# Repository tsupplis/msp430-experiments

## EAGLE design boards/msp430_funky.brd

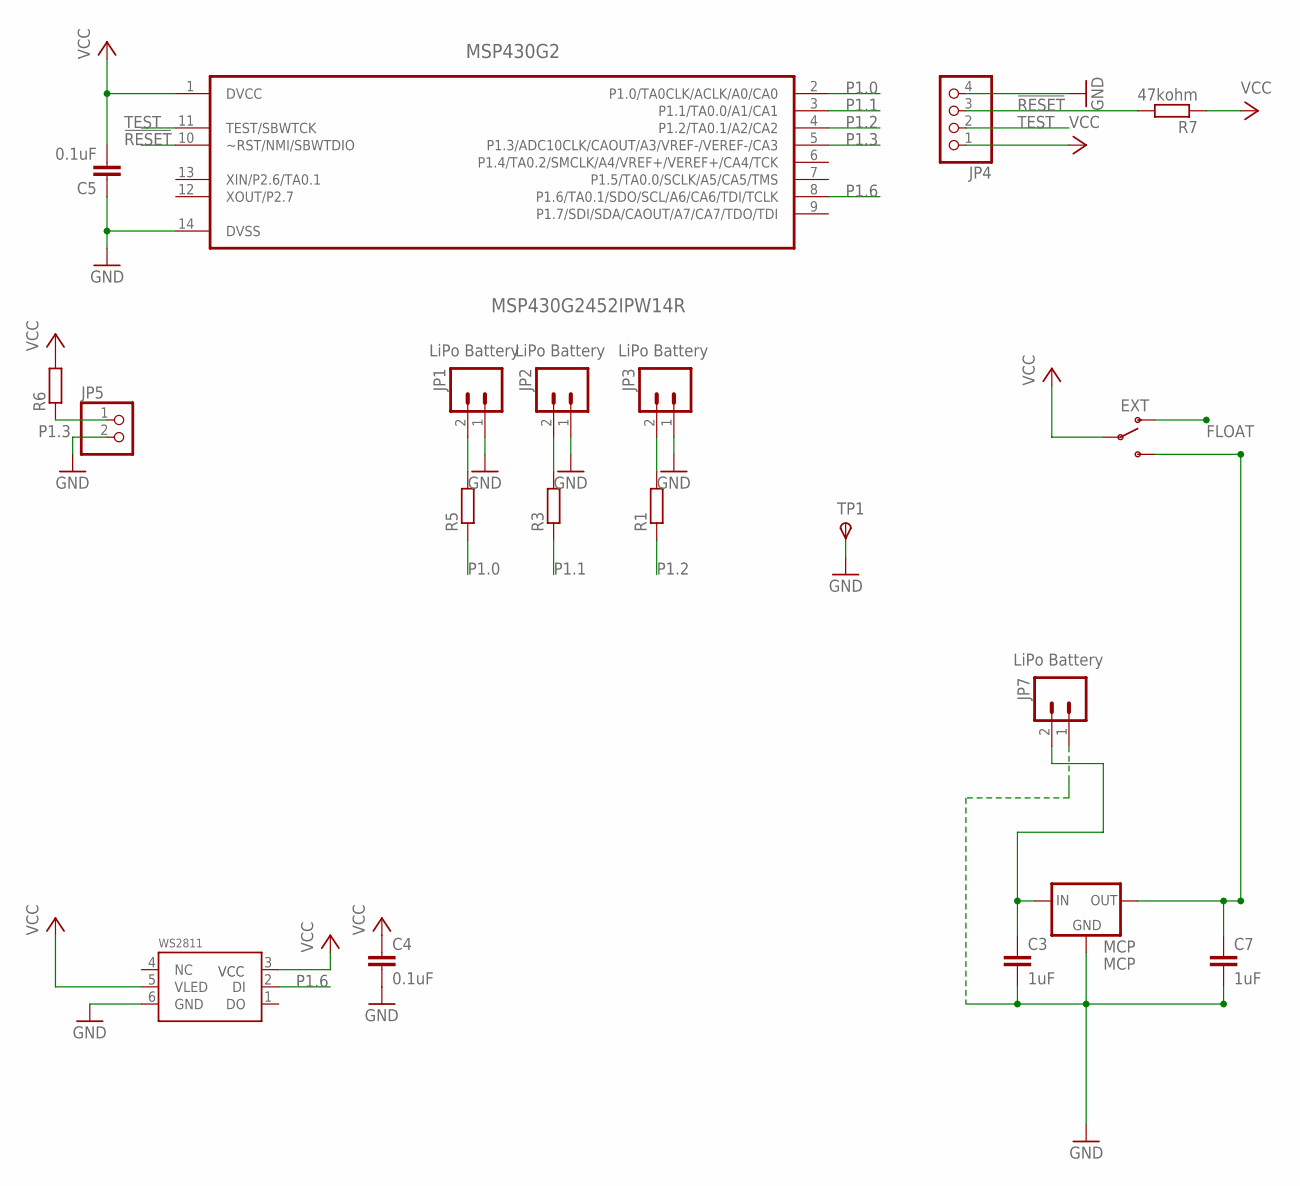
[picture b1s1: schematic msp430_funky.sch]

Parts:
C3, C7: 1uF; C0805
C4, C5: 0.1uF; C0805
JP1, JP2, JP3, JP7: LiPo Battery; JST-2-PTH
JP4: PINHD-1X4; 1X04
JP5: PINHD-1X2; 1X02
MCP: MCP; SOT-23
MSP430G2: MSP430G2452IPW14R; SOP65P640X120-14N
ON: EXT; SWITCH-SPDT
R1, R3, R5, R6: R-EU_R0805; R0805
R7: 47kohm; R0805
TP1: TPSTP20R; TP20R
WS2811: 5050WS2811W; RGBLED5050W

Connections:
!RESET: JP4.3, MSP430G2.10 (~RST/NMI/SBWTDIO), R7.2
FLOAT: ON.1 (O)
GND: C3.2, C4.2, C5.1, C7.2, JP1.1, JP2.1, JP3.1, JP4.4, JP5.2, JP7.1, MCP.1 (GND), MSP430G2.14 (DVSS), TP1.TP, WS2811.6 (GND)
unnamed: JP1.2, R5.2
unnamed: JP2.2, R3.2
unnamed: JP3.2, R1.2
P1.0: MSP430G2.2 (P1.0/TA0CLK/ACLK/A0/CA0), R5.1
P1.1: MSP430G2.3 (P1.1/TA0.0/A1/CA1), R3.1
P1.2: MSP430G2.4 (P1.2/TA0.1/A2/CA2), R1.1
P1.3: JP5.1, MSP430G2.5 (P1.3/ADC10CLK/CAOUT/A3/VREF-/VEREF-/CA3), R6.1
P1.6: MSP430G2.8 (P1.6/TA0.1/SDO/SCL/A6/CA6/TDI/TCLK), WS2811.2 (DI)
TEST: JP4.2, MSP430G2.11 (TEST/SBWTCK)
VCC: C4.1, C5.2, JP4.1, MSP430G2.1 (DVCC), ON.2, R6.2, R7.1, WS2811.3 (VCC), WS2811.5 (VLED)
VCCEXT: C3.1, JP7.2, MCP.3 (IN)
VCCREG: C7.1, MCP.2 (OUT), ON.3 (S)

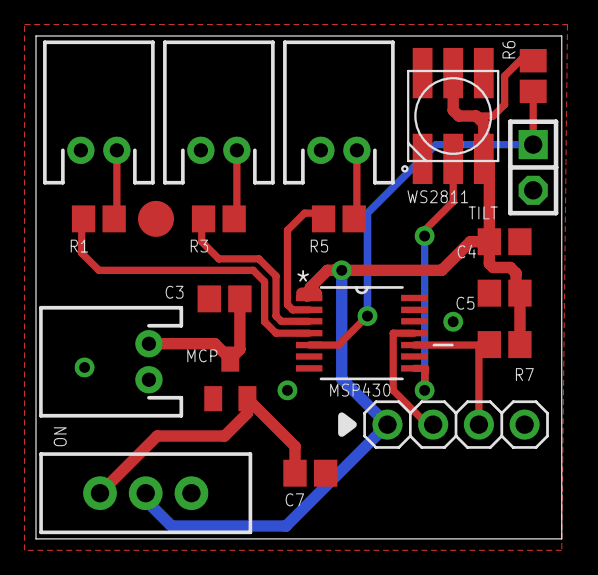
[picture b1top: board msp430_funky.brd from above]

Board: 2 copper layers, 29.2 x 27.9 mm, 20 parts (0 on the bottom side), 14 nets.

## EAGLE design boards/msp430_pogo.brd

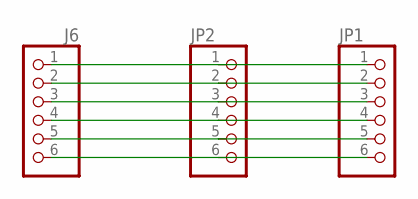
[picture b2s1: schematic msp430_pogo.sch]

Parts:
J6: PH1X650MIL; PH1X6_50MIL
JP1, JP2: PINHD-1X6; 1X06

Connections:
unnamed: J6.1, JP1.1, JP2.1
unnamed: J6.2, JP1.2, JP2.2
unnamed: J6.3, JP1.3, JP2.3
unnamed: J6.4, JP1.4, JP2.4
unnamed: J6.5, JP1.5, JP2.5
unnamed: J6.6, JP1.6, JP2.6

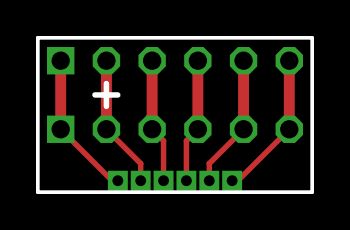
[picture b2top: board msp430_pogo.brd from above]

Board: 2 copper layers, 15.2 x 8.6 mm, 3 parts (0 on the bottom side), 6 nets.

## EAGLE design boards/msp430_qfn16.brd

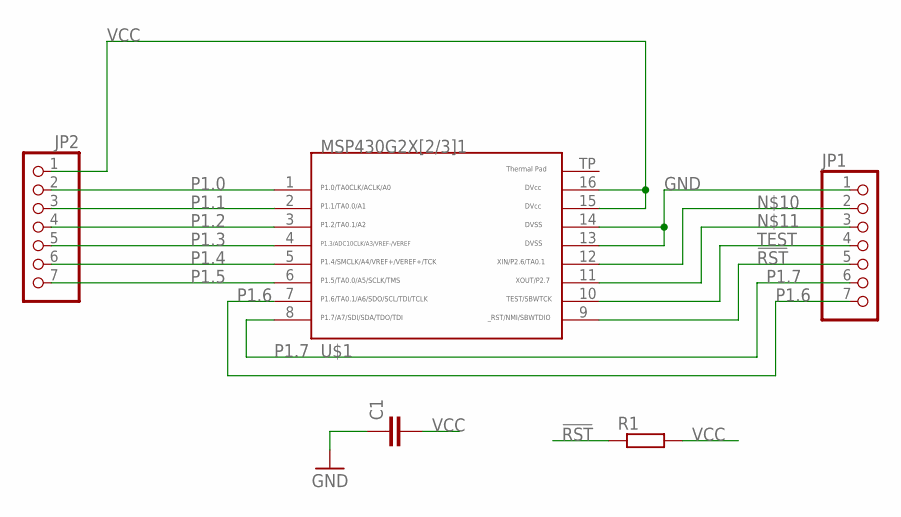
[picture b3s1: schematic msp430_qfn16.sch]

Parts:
C1: C-EUC0805K; C0805K
JP1, JP2: PINHD-1X7; 1X07
R1: R-EU_R0805; R0805
U$1: G2X[2/3]1---RSA16; RSA16

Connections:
!RST: JP1.5, R1.1, U$1.9
GND: C1.1, JP1.1, U$1.13, U$1.14
unnamed: JP1.2, U$1.12
unnamed: JP1.3, U$1.11
P1.0: JP2.2, U$1.1
P1.1: JP2.3, U$1.2
P1.2: JP2.4, U$1.3
P1.3: JP2.5, U$1.4
P1.4: JP2.6, U$1.5
P1.5: JP2.7, U$1.6
P1.6: JP1.7, U$1.7
P1.7: JP1.6, U$1.8
TEST: JP1.4, U$1.10
VCC: C1.2, JP2.1, R1.2, U$1.15, U$1.16

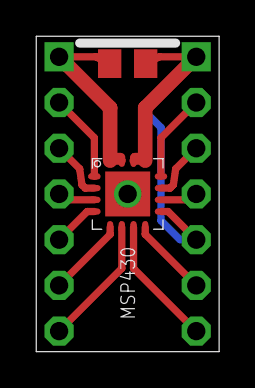
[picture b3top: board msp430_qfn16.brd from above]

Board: 2 copper layers, 10.2 x 17.5 mm, 5 parts (1 on the bottom side), 14 nets.

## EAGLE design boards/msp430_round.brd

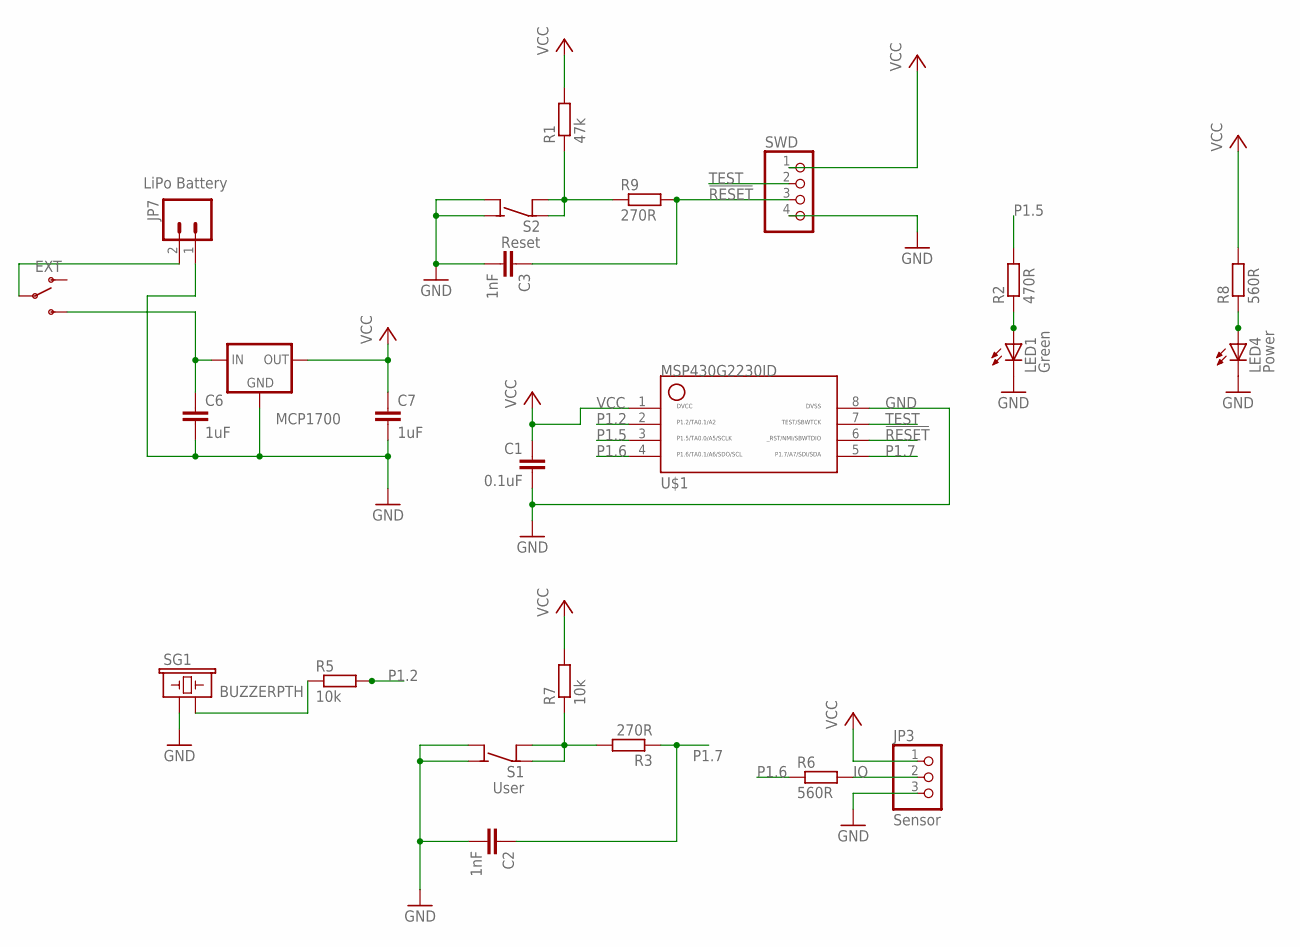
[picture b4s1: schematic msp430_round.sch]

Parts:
C1: 0.1uF; C0805
C2, C3: 1nF; C0805
C6, C7: 1uF; C0805
JP3: Sensor; 1X03
JP7: LiPo Battery; JST-2-PTH
LED1: Green; CHIPLED_1206
LED4: Power; CHIPLED_1206
MCP1700: MCP1700; SOT-23
ON: EXT; SWITCH-SPDT
R1: 47k; R0805
R2: 470R; R0805
R3, R9: 270R; R0805
R5, R7: 10k; R0805
R6, R8: 560R; R0805
S1: User; 6MMTACTILE_4PIN
S2: Reset; 6MMTACTILE_4PIN
SG1: BUZZERPTH; BUZZER-12MM
SWD: PINHD-1X4; 1X04
U$1: MSP430G2230ID; SO08

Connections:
!RESET: C3.1, R9.2, SWD.3, U$1.6
GND: C1.2, C2.2, C3.2, C6.2, C7.2, JP3.3, JP7.1, LED1.C, LED4.C, MCP1700.1 (GND), S1.A1 (NO), S1.A2 (NO), S2.A1 (NO), S2.A2 (NO), SG1.+ (1), SWD.4, U$1.8
IO: JP3.2, R6.2
unnamed: LED4.A, R8.1
unnamed: JP7.2, ON.2
unnamed: LED1.A, R2.1
unnamed: R1.1, R9.1, S2.B1 (COM), S2.B2 (COM)
unnamed: R5.1, SG1.- (2)
unnamed: R3.2, R7.1, S1.B1 (COM), S1.B2 (COM)
unnamed: C6.1, MCP1700.3 (IN), ON.3 (S)
P1.2: R5.2, U$1.2
P1.5: R2.2, U$1.3
P1.6: R6.1, U$1.4
P1.7: C2.1, R3.1, U$1.5
TEST: SWD.2, U$1.7
VCC: C1.1, C7.1, JP3.1, MCP1700.2 (OUT), R1.2, R7.2, R8.2, SWD.1, U$1.1

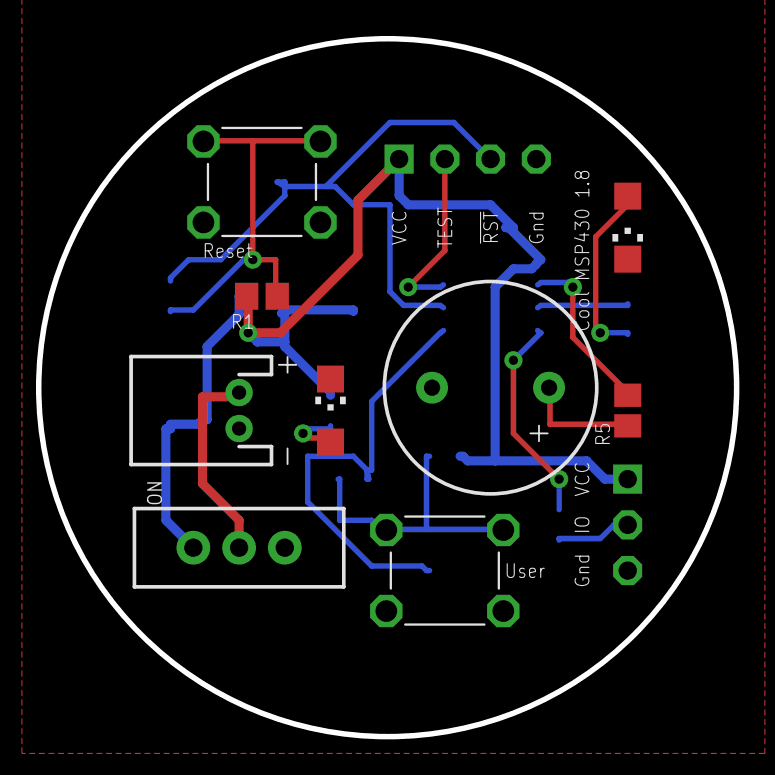
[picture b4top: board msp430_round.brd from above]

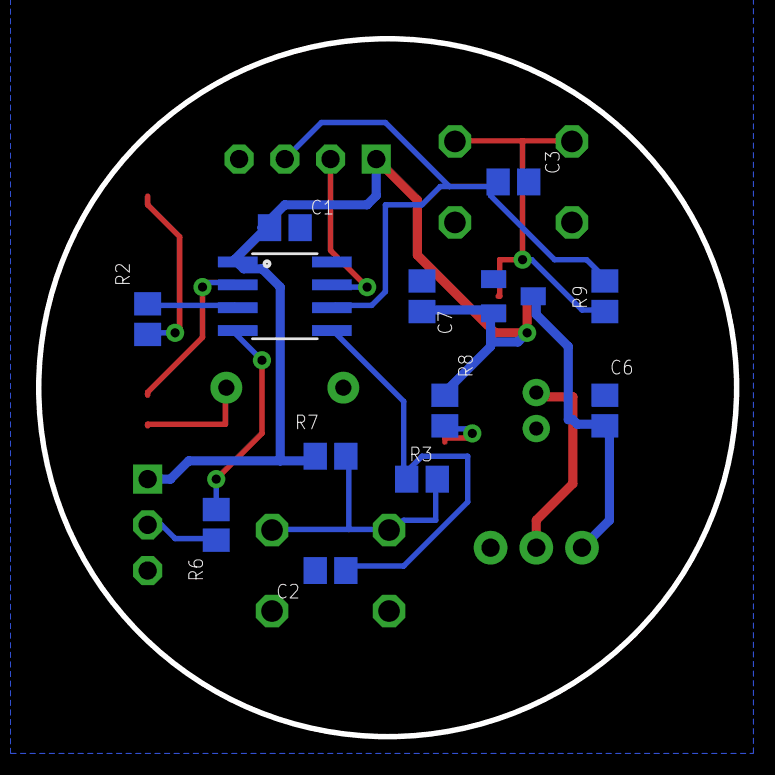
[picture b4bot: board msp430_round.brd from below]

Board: 2 copper layers, 38.8 x 38.8 mm, 24 parts (13 on the bottom side), 16 nets.

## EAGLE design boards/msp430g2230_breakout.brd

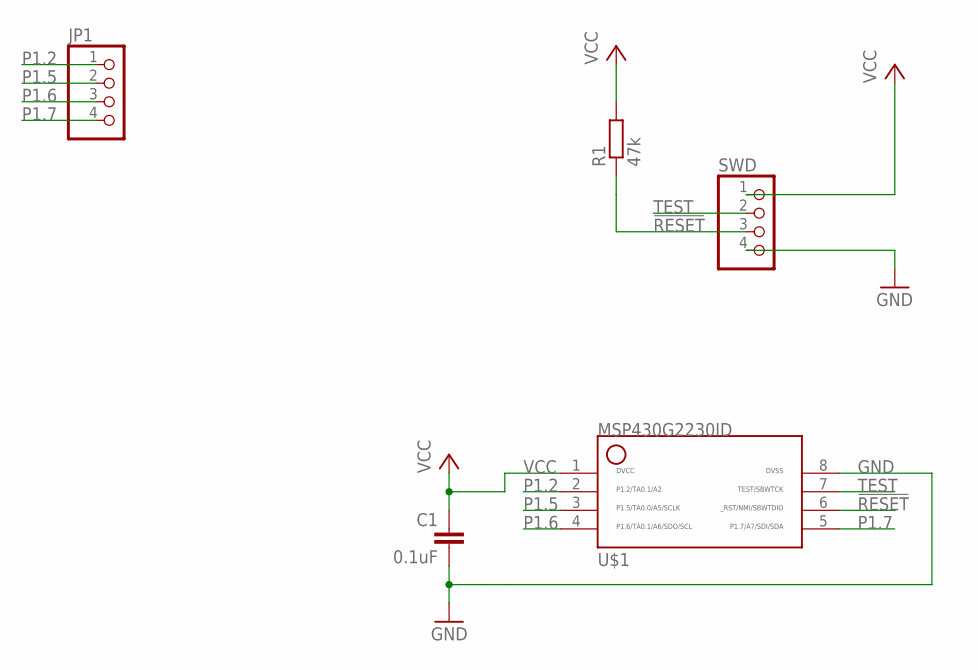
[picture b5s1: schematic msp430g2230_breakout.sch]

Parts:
C1: 0.1uF; C0805
JP1: PINHD-1X4; 1X04
R1: 47k; R0805
SWD: PINHD-1X4; 1X04
U$1: MSP430G2230ID; SO08

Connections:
!RESET: R1.1, SWD.3, U$1.6
GND: C1.2, SWD.4, U$1.8
P1.2: JP1.1, U$1.2
P1.5: JP1.2, U$1.3
P1.6: JP1.3, U$1.4
P1.7: JP1.4, U$1.5
TEST: SWD.2, U$1.7
VCC: C1.1, R1.2, SWD.1, U$1.1

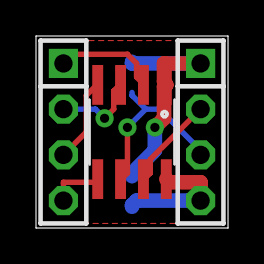
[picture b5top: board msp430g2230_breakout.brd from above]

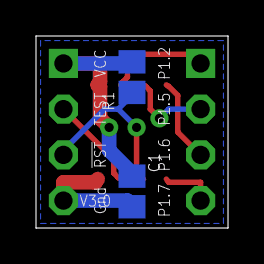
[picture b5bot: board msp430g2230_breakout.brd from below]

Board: 2 copper layers, 10.7 x 10.7 mm, 5 parts (2 on the bottom side), 8 nets.

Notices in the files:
parts and their libraries:
SparkFun: Licensing: CC v3.0 Share-Alike You are welcome to use this library for commercial purposes.
